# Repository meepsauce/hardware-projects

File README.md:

# hardware-projects
This is Repo to showcase the many small hardware projects (electronic and mechanical) I have done for school/fun. It also is just a convient place to store and share my projects across PCs.

## Projects 

- **PCB Snowflake (Christmas 2021)**

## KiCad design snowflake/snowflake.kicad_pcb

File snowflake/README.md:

# Snowflake (Christmas 2021)

One day I will fix this design... it is a very simple fix but I am lazy

## Warning:
This project works, but I do not reccomend replicating/making it in it's current state: it is very "hacky" and was made in a rush.

## Guide:

Using the supplied Gerber Files you can order the design from any manufacturer. I used JLCPCB plus their SMT service (I did not want to solder 125 LEDs by hand) and they are super cheap (plus lots of coupons). Everything, including the BOM is correct, but upon actually creating the PCB, some bodges will need to be made. I ordered my components from LCSC, and their cooresponding part numbers are in the BOM.

Soldering all the components on the board is trivial but some changes needed to be made for the board to function properly:

- Bodge GND to both decoupling capacitors that are located right below the shottcky diode.
- Bodge DOUT from the top-left arm to DIN on the first neopixel on the top arm.

## Story (Debugging and the tons of mistakes I made)
It has become a tradition of mine to create christmas themed PCBs as a gift for family/friends/teachers, etc.

In following years they have been quite simple: mostly because accounting for finals and my amazing procrastination skills, I have minimal time to actually complete the project in question.

An example is a Christmas Tree I made last year (I will find the files eventually...),  it was designed quite sloppily but was "good enough". It consisted simply of a Arduino Nano with a battery of THT LEDs and Resistors- not particularly complex but made a cool pattern.

Therefore, I wanted to naturally one-up myself and create something that utilized more technique. Thus, I arrived on the idea of a Snowflake Ornament, one that was battery powered and fully SMD. Because of the chip shortage (prices) and my familiarity with the ATtiny/ATmega family, I arrived on the Attiny84- it was cheap, simple and was capable of driving the 24 led Neopixels (4 on each arm). This is where I made my first fatal mistake however, as I assigned each arm of the snowflake (4 Neopixels) its own dedicated pin on the MCU. Not realising how little memory the Attiny84 has, this would come to bite me later...

Choosing the normal Neopixels (WS2812B) was my second mistake, as they consumed 50mA each, more like 25mA if I used a low framerate and cut the color/brightness values in half. I initally planned to power this from 2 coin cell batteries in series so the prospect of pulling possibly greater than 1A was pretty scary (in every sense). I attempted to quickly solve this by changing to the C variant (which only use ~5mA)... only to learn that they were out of stock at LCSC (I was going to use JLCPCBs SMT Services as I was out of time, and did not want to solder so many LEDs manually). Therefore I arrived on a design with a estimated power draw of ~300mA with a battery capacity of 235mAh. I was low on time, so I decided to just run with it.

Upon getting the PCBs from JLCPCB, they looked great, I choose the white mask and with the Snowflake Outline I thought it looked pretty cool (if anything, it was much larger than I imagined). However, a quick look showed that all boards were missing the MCU, a capacitor and the battery holders. I later learned that as I put the boards in production, the chips became out of stock, but JLCPCB still charged me for them. I was pissed but again, no time, and it was imperitive that I maintained my jolly behaviour. Therefore, I quickly ordered the missing components from Digikey, being in such a rush I ordered a slightly oversized battery case (which, as you may guess, became a PITA later)

After soldering the Attiny84s with a 15 dollar soldering iron (pain), I had no problem flashing them with a Arduino Uno as ISP (though I initally frogot the capacitor between RST and GND). I used the ATTiny Core Library to upload the code, I choose the correct settings for the chip I used, and did not use a discrete bootloader to save memory (and to keep it dead simple). The pin definitons were wacky but eventually through trial and error I used the FastLED library to eventually drive all arms of the snowflake, except for the top arm, it simply would not work. Frustrated I consulted my schematic and learned that for whatever reason, I thought it was a good idea to drive Neopixels using the reset pin of the Attiny84. Now, this is possible, but doing so requires setting a fuse which forces reset as a output, but therefore disables programming by ISP. Therefore I needed a better solution, and ended up cutting the trace going from the reset pin to the leds manually with a exacto knife. Then I bodged a wire from a free digital pin from the MCU to the neopixel in question. This worked, I was able to drive the arm just fine... but that's when I realised that I neglected to consider something very important: the available memory of my MCU. Upon trying to compile code that would drive every arm of the snowflake (there was a FastLED instance for each arm) I quickly came to the realization that my code was simply too big for the Attiny84. Therefore I optimized the code to the best of my ability, switching everything to unsigned ints, removing bloat code or unnessacary calls, but the code was still too big (by ~800 bytes). Therefore, seeing my mistake, my solution was actually fairly simple and worked to ease the hacky soldering of the board. I made a bodge that went from the top-left arm to the top one, then in software I doubled the amount of pins that arm was supposed to drive. This change left me using ~96% of system memory, which warned me of instability but I never encountered any problems in operation.

All that was left was power... I realised quickly that I made two big mistakes: the decoupling capacitors were not connected to ground (I honestly have not clue how I overlooked this) and the battery cases I ordered were one size too big. On my first board, I bodged the capacitors to ground, but later learned that they werent required for it to work... so I just left them as is. As for the battery cases, I forced them to work, quite literally. One of them is the wrong orientation and thus the battery needs to be flipped... but it works fine. In all, I got a battery time of ~1 hour which isnt great... but lasts long enough for people to enjoy it. I make sure to remind them that it can be powered from usb (which actually works).

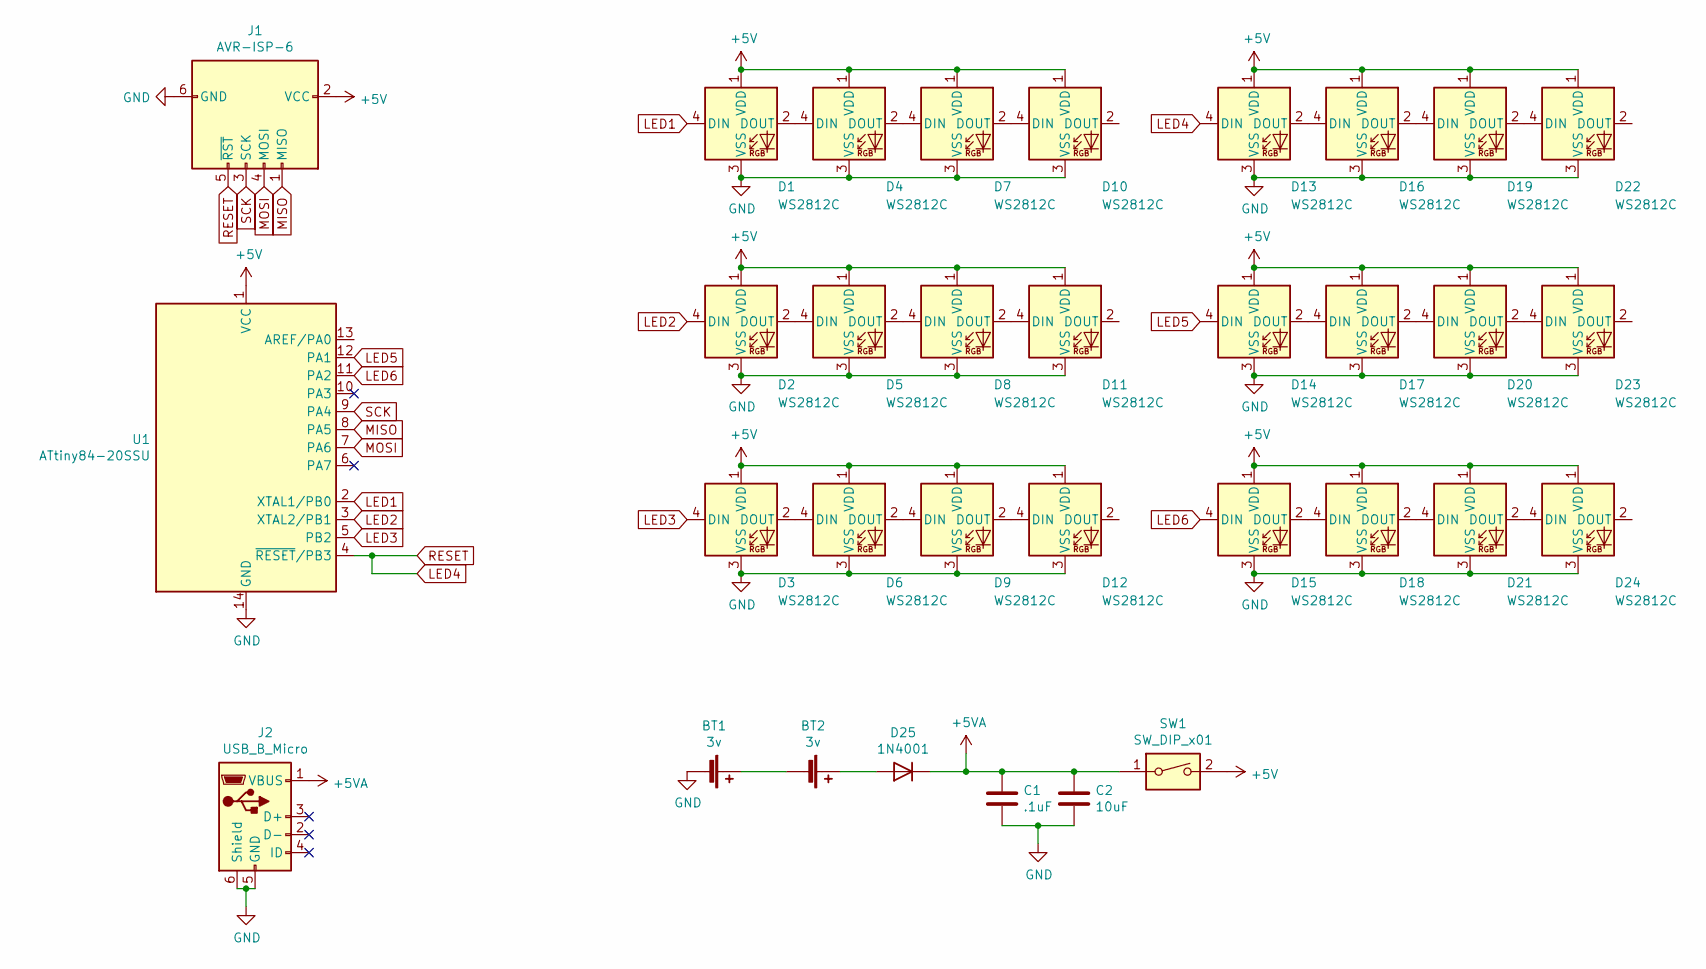
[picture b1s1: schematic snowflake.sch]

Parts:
BT1, BT2: 3v; c2032Horizontal
C1: .1uF; C_0603_1608Metric
C2: 10uF; C_0603_1608Metric
D1, D2, D3, D4, D5, D6, D7, D8, D9, D10, D11, D12, D13, D14, D15, D16, D17, D18, D19, D20, D21, D22, D23, D24: WS2812C; LED_WS2812B_PLCC4_5.0x5.0mm_P3.2mm
D25: 1N4001; D_SMA
J1: AVR-ISP-6; PinSocket_2x03_P2.54mm_Vertical
J2: USB_B_Micro; USB_Micro-B_Molex-105017-0001
SW1: SW_DIP_x01; SW_DIP_SPSTx01_Slide_6.7x4.1mm_W6.73mm_P2.54mm_LowProfile_J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
U1: ATtiny84-20SSU; SOIC-14_3.9x8.7mm_P1.27mm

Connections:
+5V: D1.1 (VDD), D2.1 (VDD), D3.1 (VDD), D4.1 (VDD), D5.1 (VDD), D6.1 (VDD), D7.1 (VDD), D8.1 (VDD), D9.1 (VDD), D10.1 (VDD), D11.1 (VDD), D12.1 (VDD), D13.1 (VDD), D14.1 (VDD), D15.1 (VDD), D16.1 (VDD), D17.1 (VDD), D18.1 (VDD), D19.1 (VDD), D20.1 (VDD), D21.1 (VDD), D22.1 (VDD), D23.1 (VDD), D24.1 (VDD), J1.2 (VCC), SW1.2, U1.1 (VCC)
+5VA: C1.1, C2.1, D25.1 (K), J2.1 (VBUS), SW1.1
GND: BT1.2 (-), C1.2, C2.2, D1.3 (VSS), D2.3 (VSS), D3.3 (VSS), D4.3 (VSS), D5.3 (VSS), D6.3 (VSS), D7.3 (VSS), D8.3 (VSS), D9.3 (VSS), D10.3 (VSS), D11.3 (VSS), D12.3 (VSS), D13.3 (VSS), D14.3 (VSS), D15.3 (VSS), D16.3 (VSS), D17.3 (VSS), D18.3 (VSS), D19.3 (VSS), D20.3 (VSS), D21.3 (VSS), D22.3 (VSS), D23.3 (VSS), D24.3 (VSS), J1.6 (GND), J2.5 (GND), J2.6 (Shield), U1.14 (GND)
LED1: D1.4 (DIN), U1.2 (XTAL1/PB0)
LED2: D2.4 (DIN), U1.3 (XTAL2/PB1)
LED3: D3.4 (DIN), U1.5 (PB2)
LED4: D13.4 (DIN), J1.5 (~RST), U1.4 (~RESET~/PB3)
LED5: D14.4 (DIN), U1.12 (PA1)
LED6: D15.4 (DIN), U1.11 (PA2)
MISO: J1.1 (MISO), U1.8 (PA5)
MOSI: J1.4 (MOSI), U1.7 (PA6)
unnamed: BT1.1 (+), BT2.2 (-)
unnamed: BT2.1 (+), D25.2 (A)
unnamed: D1.2 (DOUT), D4.4 (DIN)
unnamed: D2.2 (DOUT), D5.4 (DIN)
unnamed: D3.2 (DOUT), D6.4 (DIN)
unnamed: D4.2 (DOUT), D7.4 (DIN)
unnamed: D5.2 (DOUT), D8.4 (DIN)
unnamed: D6.2 (DOUT), D9.4 (DIN)
unnamed: D7.2 (DOUT), D10.4 (DIN)
unnamed: D8.2 (DOUT), D11.4 (DIN)
unnamed: D9.2 (DOUT), D12.4 (DIN)
unnamed: D13.2 (DOUT), D16.4 (DIN)
unnamed: D14.2 (DOUT), D17.4 (DIN)
unnamed: D15.2 (DOUT), D18.4 (DIN)
unnamed: D16.2 (DOUT), D19.4 (DIN)
unnamed: D17.2 (DOUT), D20.4 (DIN)
unnamed: D18.2 (DOUT), D21.4 (DIN)
unnamed: D19.2 (DOUT), D22.4 (DIN)
unnamed: D20.2 (DOUT), D23.4 (DIN)
unnamed: D21.2 (DOUT), D24.4 (DIN)
SCK: J1.3 (SCK), U1.9 (PA4)

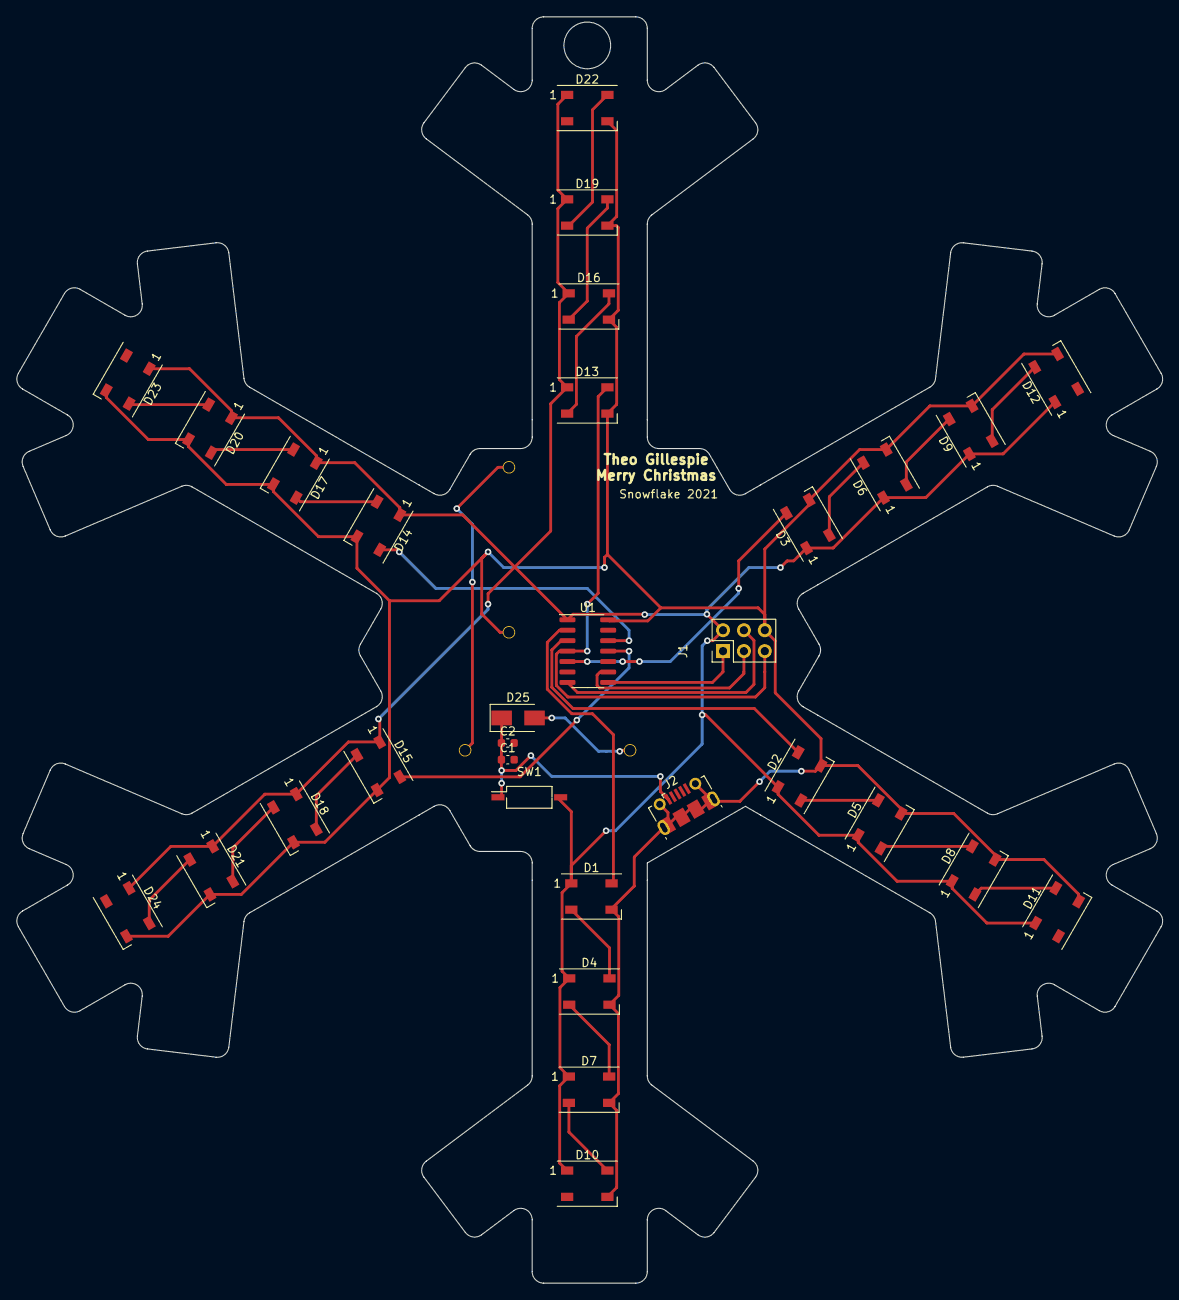
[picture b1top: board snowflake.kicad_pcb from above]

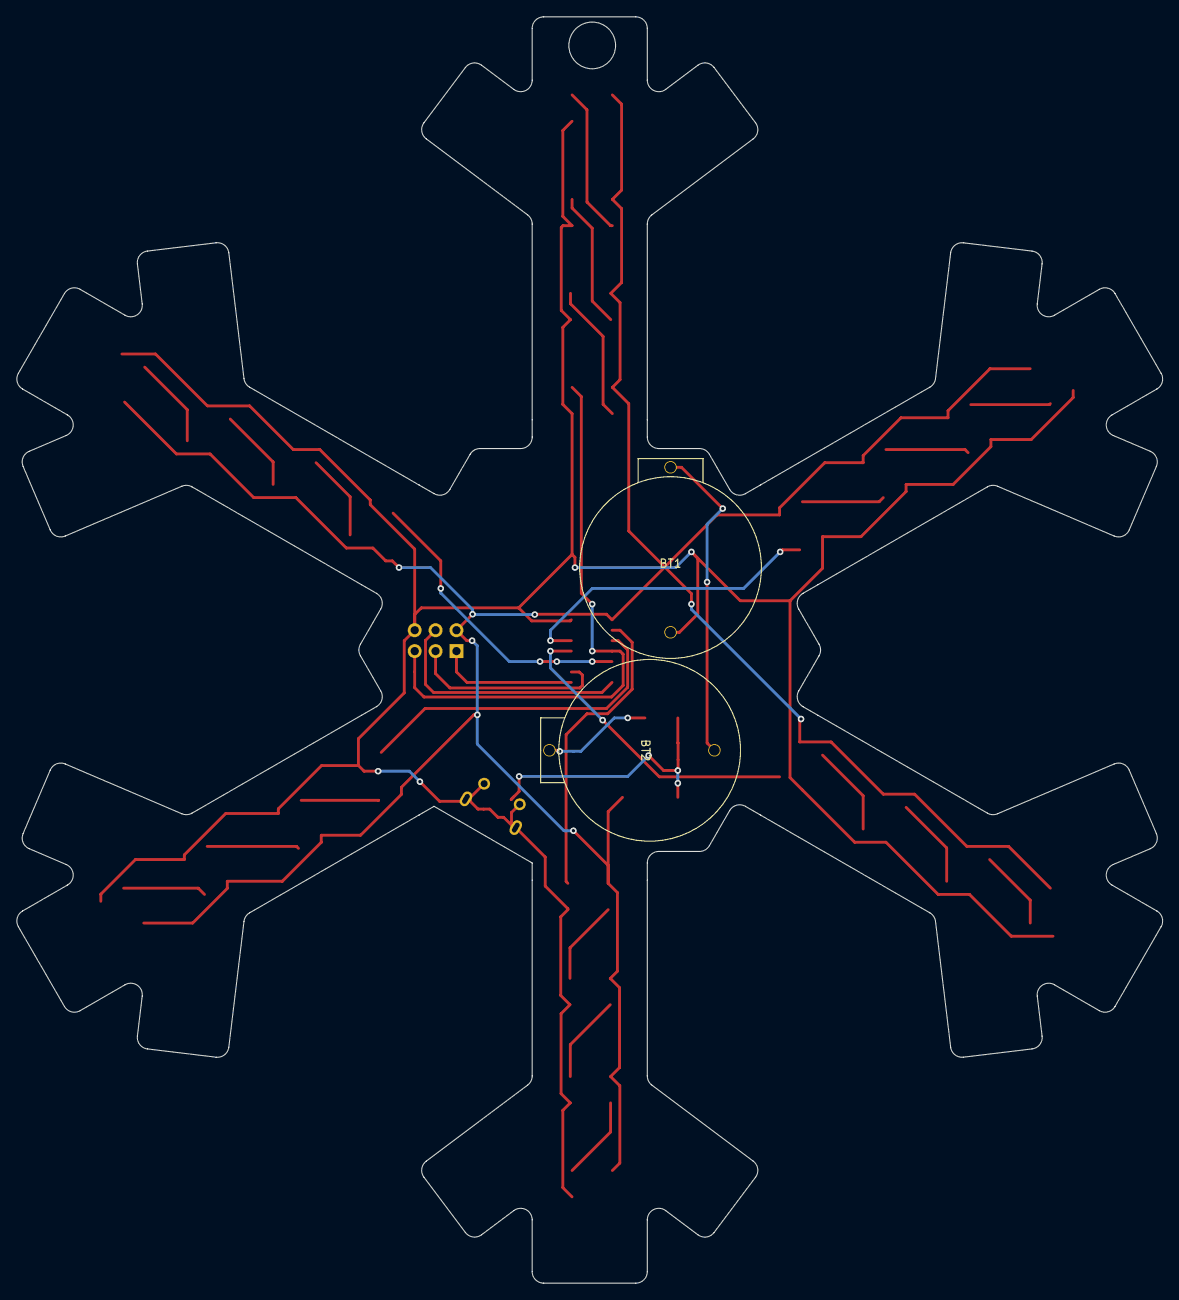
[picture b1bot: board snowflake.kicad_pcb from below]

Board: 2 copper layers, 139.3 x 154.0 mm, 33 parts (2 on the bottom side), 32 nets.

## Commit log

2022-01-04 Create snowflake
2022-01-04 Added snowflake project outline
2022-01-04 added some projects that are in progress
2022-01-05 Added snowflake files, added station files
